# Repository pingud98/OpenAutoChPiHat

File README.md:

# OpenAutoChPiHat
A Raspberry Pi Hat designed for open hardware and open software car sharing

It's now featured in the SEEED fusion gallery: https://www.seeedstudio.com/Open-Car-Sharing-Hardware-Module-OpenAuto-c-g-1036303

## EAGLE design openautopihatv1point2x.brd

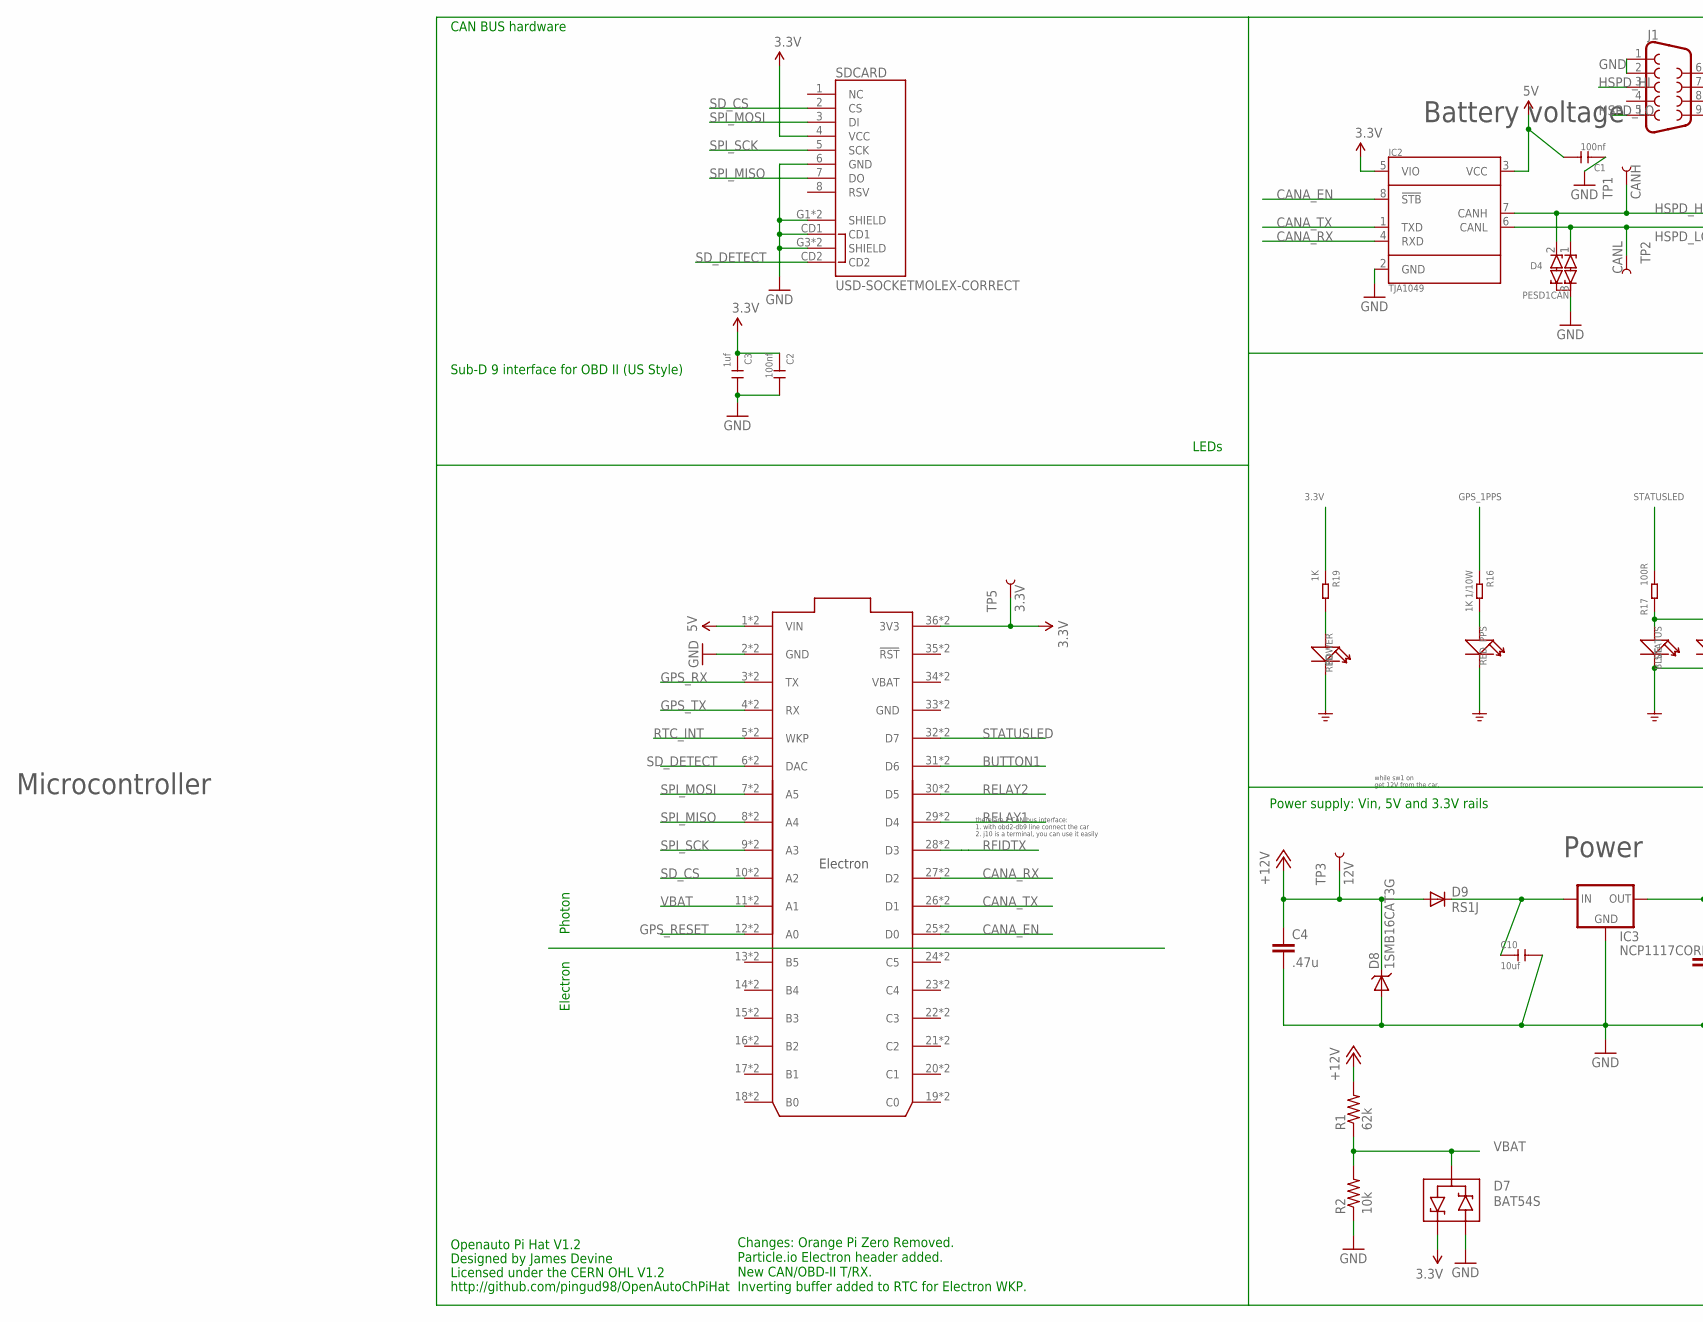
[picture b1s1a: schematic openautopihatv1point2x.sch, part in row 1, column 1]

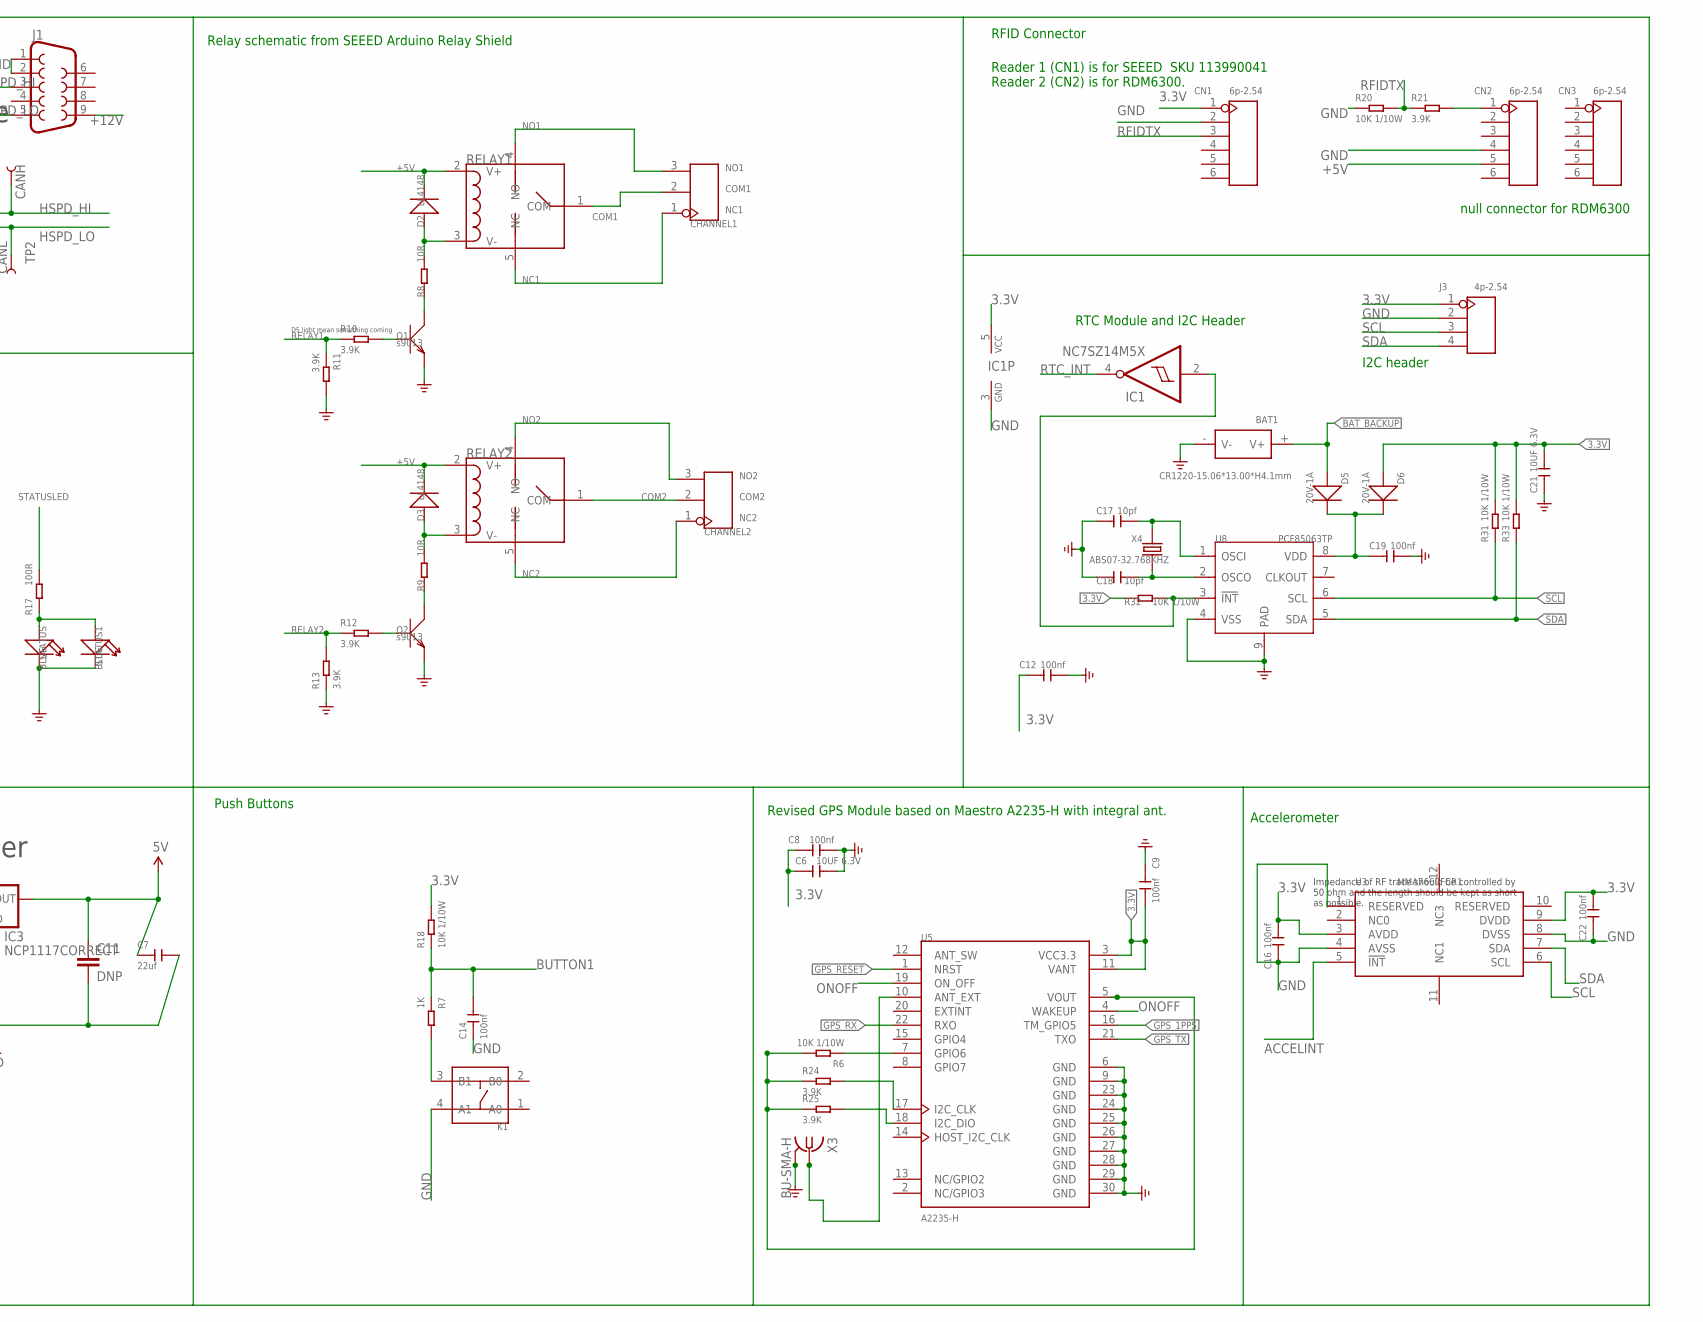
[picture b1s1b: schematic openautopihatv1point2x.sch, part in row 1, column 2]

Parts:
BAT1: CR1220-15.06*13.00*H4.1mm; BAT2P-SMD-16.4-CR1220
C1, C2: 100nf; C0603; PARTNO 08055C104KAT2A
C3: 1uf; C0603; PARTNO CC0805KKX7R7BB105
C4: .47u; C0805; PARTNO C0805C474K5RACTU
C6, C21: 10UF 6.3V; C0603
C7: 22uf; C0805; PARTNO GRM219R61A226MEA0D
C8, C9, C12, C14, C16, C19, C22: 100nf; C0603
C10: 10uf; C0805; PARTNO GRM21BR6YA106KE43L
C11: DNP; C0805; PARTNO GRM219R61A226MEA0D
C17, C18: 10pf; C0603
CHANNEL1, CHANNEL2: SCREW-TERMINAL-3P'3.5'; 3P-3.5
CN1, CN2, CN3: 6p-2.54; H6-2.54
D2, D3: LL4148; LL-34
D4: PESD1CAN; SOT23; PARTNO PESD1CAN-215
D5, D6: 20V-1A; SOD-123
D7: BAT54S; SOT23; PARTNO BAT54S-7-F
D8: 1SMB16CAT3G; SMB-DIODE; PARTNO 1SMB16CAT3G
D9: RS1J; SMA-DIODE; PARTNO RS1J-E3/5AT
ELECTRON: ELECTRON_WITH_EXTERNAL_HEADERS; ELECTRON_EXTERNAL; PARTNO PPTC181LFBN-RC
IC1: NC7SZ14M5X; SOT23-5
IC2: TJA1049; SO8; PARTNO TJA1049T-118
IC3: NCP1117CORRECT; SOT223; PARTNO NCP1117LPST50T3G
J1: DB9MALE; DB9_MALE
J3: 4p-2.54; H4-2.54
K1: DIP-SWITCH-TACTILE-SPST-NO/TS-1109(4P-D6.0MM)'TS-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; SW4-6.0X6.0X5.0MM
POWER: RED; LED-0603
PPS: RED; LED-0603
Q1, Q2: s9013; SOT23
R1: 62k; R0805; PARTNO ERJ-6ENF6202V
R2: 10k; R0805; PARTNO ERJ-6ENF1002V
R6, R18, R20, R31, R32, R33: 10K 1/10W; R0603
R7, R19: 1K; R0603
R8, R9: 10R; R0603
R10, R11, R12, R13, R21, R24, R25: 3.9K; R0603
R16: 1K 1/10W; R0603
R17: 100R; R0603
RELAY1, RELAY2: RELAY-HLS8L-DC5V-S-C; 5P-19.0X15.5X15.8H
SDCARD: USD-SOCKETMOLEX-CORRECT; MICRO-SD-MOLEX-CORRECT; PARTNO 1040310811
STATUS, STATUS1: BLUE; LED-0603
TP1: CANH; PAD.03X.03
TP2: CANL; PAD.03X.03
TP3: 12V; PAD.03X.03
TP5: 3.3V; PAD.03X.03
U3: MMA7660FCR1; DFN10-0.5-3.0X3.0MM
U5: A2235-H; XCVR_A2235-H
U8: PCF85063TP; HWSON8-0.5-2X3X0.75MM
X3: BU-SMA-H
X4: ABS07-32.768KHZ; X2-SMD-3.2X1.5X0.55MM

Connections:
3.3V: C2.1, C3.1, C6.1, C8.1, C9.2, C12.1, C16.2, C21.2, C22.2, CN1.1, D6.+, D7.2 (C1), ELECTRON.36 (3V3), ELECTRON.@36 (3V3), IC1.5 (VCC), IC2.5 (VIO), J3.1, R18.2, R19.1, R31.2, R32.1, R33.2, SDCARD.4 (VCC), TP5.P$1, U3.3 (AVDD), U3.9 (DVDD), U5.3 (VCC3.3), U5.11 (VANT)
5V: C1.2, C7.1, C11.1, ELECTRON.1 (VIN), ELECTRON.@1 (VIN), IC2.3 (VCC), IC3.2 (OUT), IC3.4 (OUT)
!RTC_INT: IC1.2 (I), R32.2, U8.3 (!INT)
+5V: CN2.5, D2.C (-), D3.C (-), RELAY1.2 (V+), RELAY2.2 (V+)
+12V: C4.1, D8.C, D9.A, J1.9, R1.2, TP3.P$1
ACCELINT: U3.5 (!INT)
BAT_BACKUP: BAT1.+ (V+), D5.+
BUTTON1: C14.2, ELECTRON.31 (D6), ELECTRON.@31 (D6), R7.1, R18.1
CANA_EN: ELECTRON.25 (D0), ELECTRON.@25 (D0), IC2.8 (!STB)
CANA_RX: ELECTRON.27 (D2), ELECTRON.@27 (D2), IC2.4 (RXD)
CANA_TX: ELECTRON.26 (D1), ELECTRON.@26 (D1), IC2.1 (TXD)
COM1: CHANNEL1.2, RELAY1.1 (COM)
COM2: CHANNEL2.2, RELAY2.1 (COM)
GND: BAT1.- (V-), C1.1, C2.2, C3.2, C4.2, C6.2, C7.2, C8.2, C9.1, C10.2, C11.2, C12.2, C14.1, C16.1, C17.1, C18.1, C19.2, C21.1, C22.1, CN1.2, CN2.4, D4.3 (COM), D7.1 (A2), D8.A, ELECTRON.2 (GND), ELECTRON.33 (GND), ELECTRON.@2 (GND), ELECTRON.@33 (GND), IC1.3 (GND), IC2.2 (GND), IC3.1 (GND), J1.1, J1.2, J3.2, K1.4 (A1), POWER.-, PPS.-, Q1.2 (E), Q2.2 (E), R2.1, R11.2, R13.1, R20.1, SDCARD.6 (GND), SDCARD.CD1, SDCARD.G1 (SHIELD), SDCARD.G2 (SHIELD), SDCARD.G3 (SHIELD), SDCARD.G4 (SHIELD), STATUS.-, STATUS1.-, U3.1 (RESERVED), U3.4 (AVSS), U3.8 (DVSS), U5.6 (GND), U5.9 (GND), U5.23 (GND), U5.24 (GND), U5.25 (GND), U5.26 (GND), U5.27 (GND), U5.28 (GND), U5.29 (GND), U5.30 (GND), U8.4 (VSS), U8.9 (PAD), X3.2, X3.3 (2), X3.4 (2), X3.5 (2)
GPS_1PPS: R16.1, U5.16 (TM_GPIO5)
GPS_RESET: ELECTRON.12 (A0), ELECTRON.@12 (A0), U5.1 (NRST)
GPS_RX: ELECTRON.3 (TX), ELECTRON.@3 (TX), U5.22 (RXO)
GPS_TX: ELECTRON.4 (RX), ELECTRON.@4 (RX), U5.21 (TXO)
HSPD_HI: D4.2 (C2), IC2.7 (CANH), J1.3, TP1.P$1
HSPD_LO: D4.1 (C1), IC2.6 (CANL), J1.5, TP2.P$1
unnamed: K1.3 (B1), R7.2
unnamed: Q2.1 (B), R12.2
unnamed: D3.A (+), R9.2, RELAY2.3 (V-)
unnamed: Q1.3 (C), R8.1
unnamed: D2.A (+), R8.2, RELAY1.3 (V-)
unnamed: Q2.3 (C), R9.1
unnamed: PPS.+, R16.2
unnamed: R17.2, STATUS.+, STATUS1.+
unnamed: U5.10 (ANT_EXT), X3.1
unnamed: R6.2, R24.1, R25.1, U5.5 (VOUT)
unnamed: R6.1, U5.7 (GPIO6)
unnamed: Q1.1 (B), R10.2
unnamed: CN2.1, R21.2
unnamed: R24.2, U5.17 (I2C_CLK)
unnamed: R25.2, U5.18 (I2C_DIO)
unnamed: POWER.+, R19.2
unnamed: C18.2, U8.2 (OSCO), X4.1
unnamed: C17.2, U8.1 (OSCI), X4.2
unnamed: C10.1, D9.C, IC3.3 (IN)
unnamed: C19.1, D5.-, D6.-, U8.8 (VDD)
NC1: CHANNEL1.1, RELAY1.5 (NC)
NC2: CHANNEL2.1, RELAY2.5 (NC)
NO1: CHANNEL1.3, RELAY1.4 (NO)
NO2: CHANNEL2.3, RELAY2.4 (NO)
ONOFF: U5.4 (WAKEUP), U5.19 (ON_OFF)
RELAY1: ELECTRON.29 (D4), ELECTRON.@29 (D4), R10.1, R11.1
RELAY2: ELECTRON.30 (D5), ELECTRON.@30 (D5), R12.1, R13.2
RFIDTX: CN1.3, ELECTRON.28 (D3), ELECTRON.@28 (D3), R20.2, R21.1
RTC_INT: ELECTRON.5 (WKP), ELECTRON.@5 (WKP), IC1.4 (O)
SCL: J3.3, R31.1, U3.6 (SCL), U8.6 (SCL)
SDA: J3.4, R33.1, U3.7 (SDA), U8.5 (SDA)
SD_CS: ELECTRON.10 (A2), ELECTRON.@10 (A2), SDCARD.2 (CS)
SD_DETECT: ELECTRON.6 (DAC), ELECTRON.@6 (DAC), SDCARD.CD2
SPI_MISO: ELECTRON.8 (A4), ELECTRON.@8 (A4), SDCARD.7 (DO)
SPI_MOSI: ELECTRON.7 (A5), ELECTRON.@7 (A5), SDCARD.3 (DI)
SPI_SCK: ELECTRON.9 (A3), ELECTRON.@9 (A3), SDCARD.5 (SCK)
STATUSLED: ELECTRON.32 (D7), ELECTRON.@32 (D7), R17.1
VBAT: D7.3 (COM), ELECTRON.11 (A1), ELECTRON.34 (VBAT), ELECTRON.@11 (A1), ELECTRON.@34 (VBAT), R1.1, R2.2

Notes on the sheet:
D5 light mean something coming
CAN BUS hardware
there are 2 CAN bus interface:
1. with obd2-db9 line connect the car
2. j10 is a terminal, you can use it easily
Sub-D 9 interface for OBD II (US Style)
get 12V from the car,
while sw1 on
Relay schematic from SEEED Arduino Relay Shield
RFID Connector
Reader 1 (CN1) is for SEEED SKU 113990041 Reader 2 (CN2) is for RDM6300.
RTC Module and I2C Header
Impedance of RF trace should be controlled by 50 ohm and the length should be kept as short as possible.
Revised GPS Module based on Maestro A2235-H with integral ant.
LEDs
Openauto Pi Hat V1.2
Designed by James Devine
Licensed under the CERN OHL V1.2
http://github.com/pingud98/OpenAutoChPiHat
Changes: Orange Pi Zero Removed. Particle.io Electron header added. New CAN/OBD-II T/RX. Inverting buffer added to RTC for Electron WKP.
Push Buttons
Accelerometer
Power supply: Vin, 5V and 3.3V rails
null connector for RDM6300
I2C header
Battery voltage
Microcontroller
Power
Photon
Electron

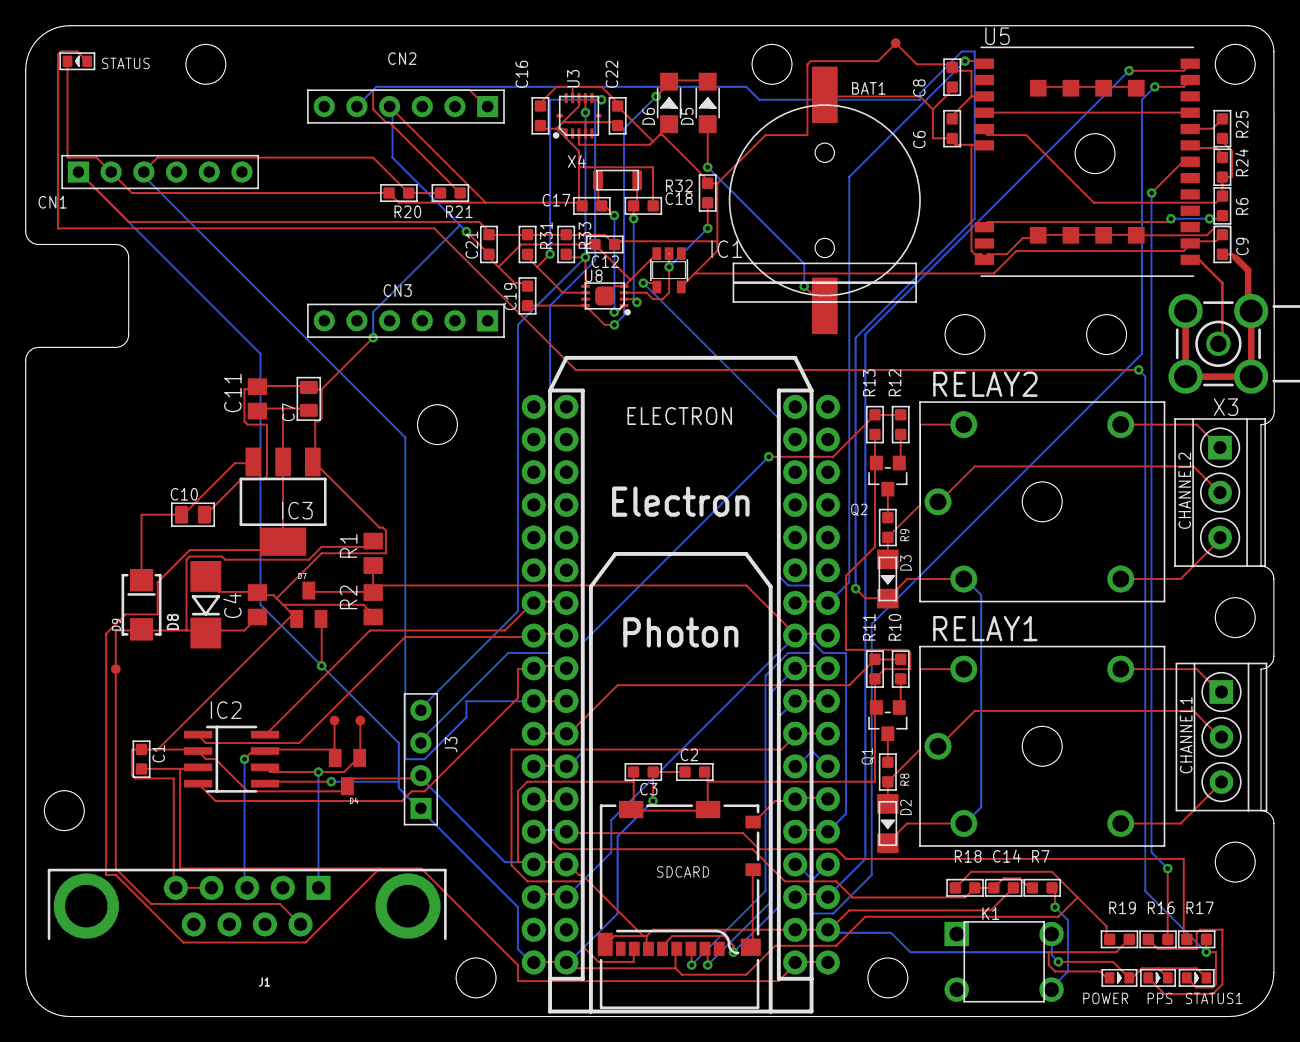
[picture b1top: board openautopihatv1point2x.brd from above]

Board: 2 copper layers, 97.0 x 77.0 mm, 78 parts (0 on the bottom side), 57 nets.

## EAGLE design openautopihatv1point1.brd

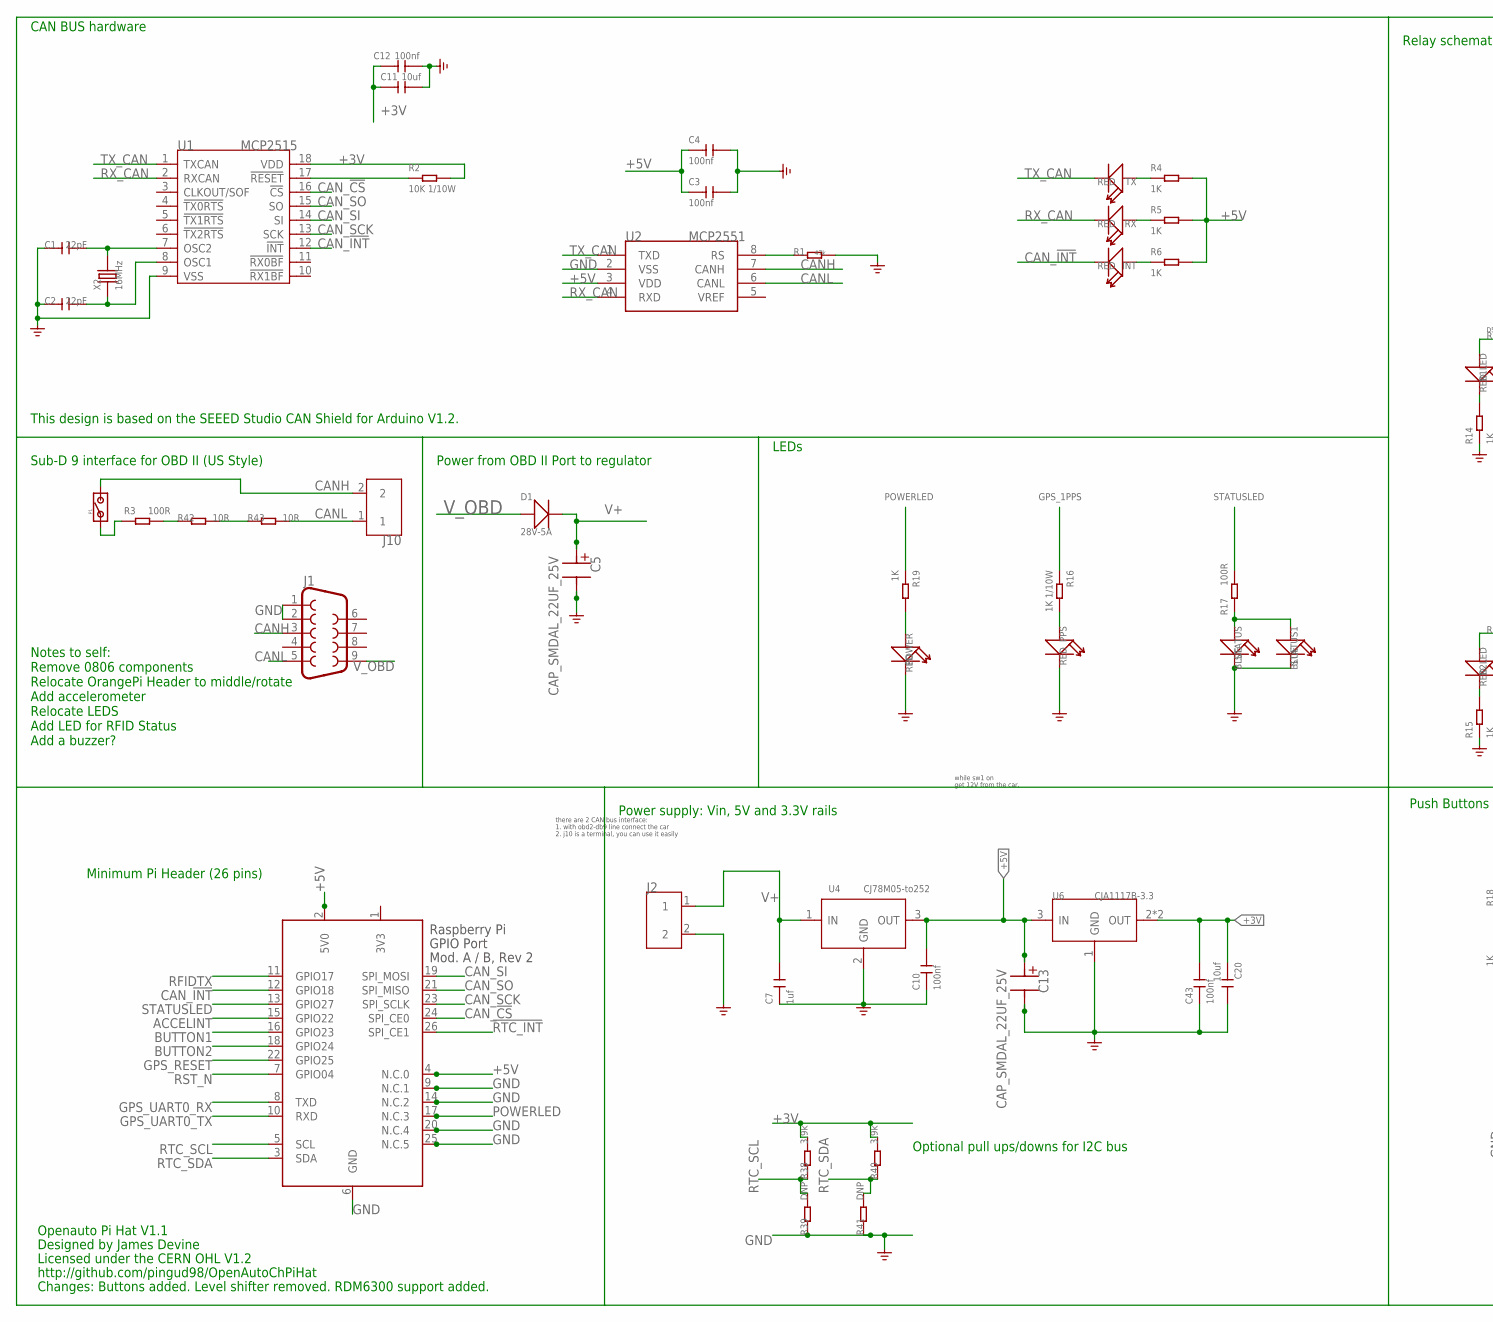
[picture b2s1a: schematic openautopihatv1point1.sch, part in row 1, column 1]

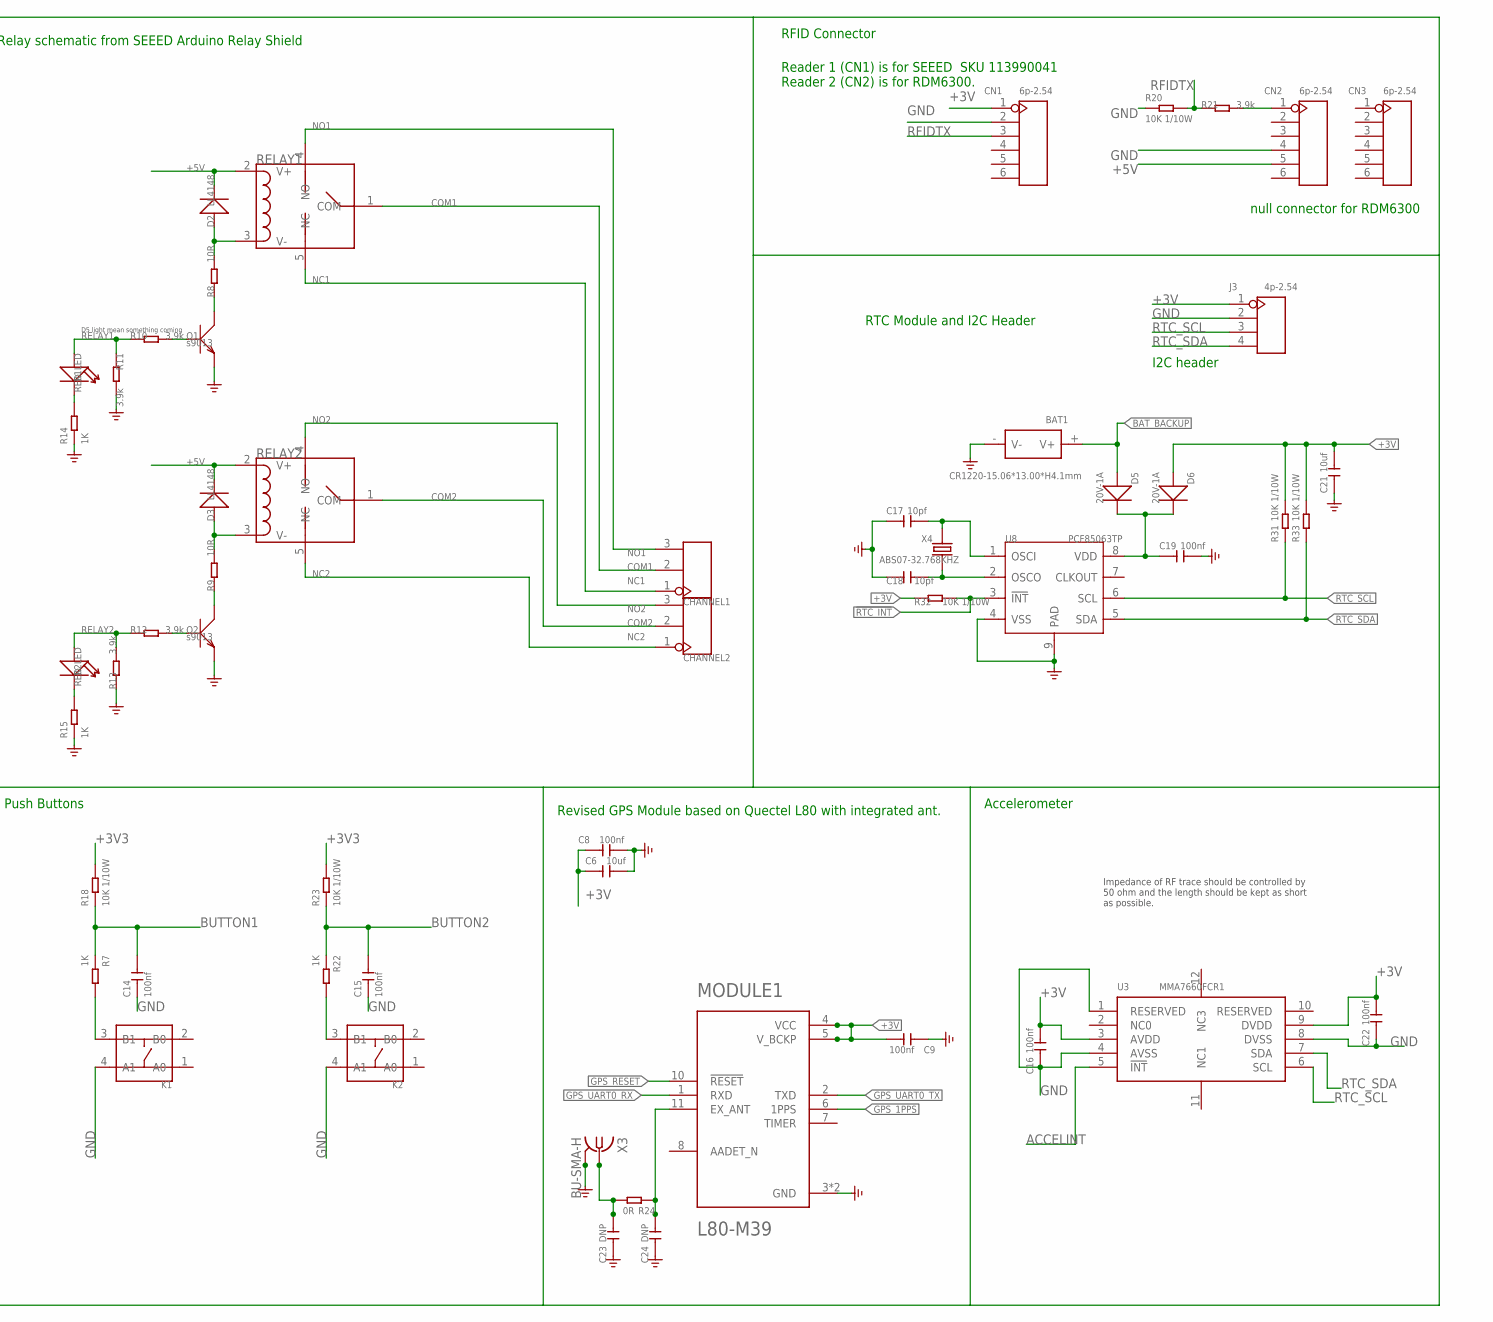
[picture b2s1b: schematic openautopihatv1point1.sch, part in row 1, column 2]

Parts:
BAT1: CR1220-15.06*13.00*H4.1mm; BAT2P-SMD-16.4-CR1220
C1, C2: 22pF; C0603
C3, C4, C8, C9, C10, C12, C14, C15, C16, C19, C22, C43: 100nf; C0603
C5, C13: CAP_SMDAL_22UF_25V; CAP_SMD_AL_D50
C6, C11, C20, C21: 10uf; C0805
C7: 1uf; C0603
C17, C18: 10pf; C0603
C23, C24: DNP; C0603
CHANNEL1, CHANNEL2: SCREW-TERMINAL-3P'3.5'; 3P-3.5
CN1, CN2, CN3: 6p-2.54; H6-2.54
D1: 28V-5A; DO-214AA
D2, D3: LL4148; LL-34
D5, D6: 20V-1A; SOD-123
INT: RED; LED-0603
J1: DB9MALE; DB9_MALE
J2, J10: SCREW-TERMINAL-2P5.0; 2P-5.0
J3: 4p-2.54; H4-2.54
K1, K2: DIP-SWITCH-TACTILE-SPST-NO/TS-1109(4P-D6.0MM)'TS-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; SW4-6.0X6.0X5.0MM
MODULE1: L80-M39; QUECTEL_L80-M39
P1: PAD-JUMPER-2P; 2P-SMD-1.78X1.27
POWER: RED; LED-0603
PPS: RED; LED-0603
Q1, Q2: s9013; SOT23
R1: 47k; 0603
R1LED, R2LED: RED; LED-0603
R2, R18, R20, R23, R31, R32, R33: 10K 1/10W; R0603
R3, R17: 100R; R0603
R4, R5, R6, R7, R14, R15, R19, R22: 1K; R0603
R8, R9, R42, R43: 10R; R0603
R10, R11, R12, R13, R21, R38, R40: 3.9k; R0603
R16: 1K 1/10W; R0603
R24: 0R; R0603
R39, R41: DNP; R0603
RELAY1, RELAY2: RELAY-HLS8L-DC5V-S-C; 5P-19.0X15.5X15.8H
RX: RED; LED-0603
STATUS, STATUS1: BLUE; LED-0603
TX: RED; LED-0603
U1: MCP2515; SOIC18
U2: MCP2551; SOIC8-6.0
U3: MMA7660FCR1; DFN10-0.5-3.0X3.0MM
U4: CJ78M05-to252; TO-252
U6: CJA1117B-3.3; SOT-89
U8: PCF85063TP; HWSON8-0.5-2X3X0.75MM
X1: RASPI_GPIO_AB_PIN
X2: 16MHz; HC49/S
X3: BU-SMA-H
X4: ABS07-32.768KHZ; X2-SMD-3.2X1.5X0.55MM

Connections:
3V3: X1.1 (3V3)
!RTC_INT: R32.2, U8.3 (!INT), X1.26 (SPI_CE1)
+3V: C6.1, C8.1, C9.2, C11.1, C12.1, C16.2, C20.1, C21.2, C22.2, C43.2, CN1.1, D6.+, J3.1, MODULE1.4 (VCC), MODULE1.5 (V_BCKP), R2.2, R31.2, R32.1, R33.2, R38.2, R40.2, U1.18 (VDD), U3.3 (AVDD), U3.9 (DVDD), U6.2 (OUT), U6.4 (OUT)
+3V3: R18.2, R23.2
+5V: C3.1, C4.1, C10.2, C13.P$P, CN2.5, D2.C (-), D3.C (-), R4.2, R5.2, R6.2, RELAY1.2 (V+), RELAY2.2 (V+), U2.3 (VDD), U4.3 (OUT), U6.3 (IN), X1.2 (5V0), X1.4 (N.C.0)
ACCELINT: U3.5 (!INT), X1.15 (GPIO22)
BAT_BACKUP: BAT1.+ (V+), D5.+
BUTTON1: C14.2, R7.1, R18.1, X1.16 (GPIO23)
BUTTON2: C15.2, R22.1, R23.1, X1.18 (GPIO24)
CANH: J1.3, J10.2, P1.2, U2.7 (CANH)
CANL: J1.5, J10.1, R43.2, U2.6 (CANL)
CAN_!CS: U1.16 (!CS), X1.24 (SPI_CE0)
CAN_!INT: INT.-, U1.12 (!INT), X1.12 (GPIO18)
CAN_SCK: U1.13 (SCK), X1.23 (SPI_SCLK)
CAN_SI: U1.14 (SI), X1.19 (SPI_MOSI)
CAN_SO: U1.15 (SO), X1.21 (SPI_MISO)
COM1: CHANNEL1.2, RELAY1.1 (COM)
COM2: CHANNEL2.2, RELAY2.1 (COM)
GND: BAT1.- (V-), C1.1, C2.1, C3.2, C4.2, C5.P$M, C6.2, C7.1, C8.2, C9.1, C10.1, C11.2, C12.2, C13.P$M, C14.1, C15.1, C16.1, C17.1, C18.1, C19.2, C20.2, C21.1, C22.1, C23.1, C24.1, C43.1, CN1.2, CN2.4, J1.1, J1.2, J2.2, J3.2, K1.4 (A1), K2.4 (A1), MODULE1.3 (GND), MODULE1.12 (GND), POWER.-, PPS.-, Q1.2 (E), Q2.2 (E), R1.2, R11.2, R13.1, R14.1, R15.1, R20.1, R39.1, R41.1, STATUS.-, STATUS1.-, U1.9 (VSS), U2.2 (VSS), U3.1 (RESERVED), U3.4 (AVSS), U3.8 (DVSS), U4.2 (GND), U6.1 (GND), U8.4 (VSS), U8.9 (PAD), X1.6 (GND), X1.9 (N.C.1), X1.14 (N.C.2), X1.20 (N.C.4), X1.25 (N.C.5), X3.2, X3.3 (2), X3.4 (2), X3.5 (2)
GPS_1PPS: MODULE1.6 (1PPS), R16.1
GPS_RESET: MODULE1.10 (!RESET), X1.22 (GPIO25)
GPS_UART0_RX: MODULE1.1 (RXD), X1.8 (TXD)
GPS_UART0_TX: MODULE1.2 (TXD), X1.10 (RXD)
unnamed: K1.3 (B1), R7.2
unnamed: R4.1, TX.+
unnamed: Q2.1 (B), R12.2
unnamed: D3.A (+), R9.2, RELAY2.3 (V-)
unnamed: Q1.3 (C), R8.1
unnamed: D2.A (+), R8.2, RELAY1.3 (V-)
unnamed: Q2.3 (C), R9.1
unnamed: PPS.+, R16.2
unnamed: R17.2, STATUS.+, STATUS1.+
unnamed: R3.1, R42.1
unnamed: R1LED.-, R14.2
unnamed: R2LED.-, R15.2
unnamed: C24.2, MODULE1.11 (EX_ANT), R24.1
unnamed: R5.1, RX.+
unnamed: C1.2, U1.7 (OSC2), X2.2
unnamed: C2.2, U1.8 (OSC1), X2.1
unnamed: C23.2, R24.2, X3.1
unnamed: INT.+, R6.1
unnamed: R1.1, U2.8 (RS)
unnamed: Q1.1 (B), R10.2
unnamed: CN2.1, R21.2
unnamed: K2.3 (B1), R22.2
unnamed: POWER.+, R19.2
unnamed: P1.1, R3.2
unnamed: C18.2, U8.2 (OSCO), X4.1
unnamed: C17.2, U8.1 (OSCI), X4.2
unnamed: R42.2, R43.1
unnamed: C19.1, D5.-, D6.-, U8.8 (VDD)
NC1: CHANNEL1.1, RELAY1.5 (NC)
NC2: CHANNEL2.1, RELAY2.5 (NC)
NO1: CHANNEL1.3, RELAY1.4 (NO)
NO2: CHANNEL2.3, RELAY2.4 (NO)
POWERLED: R19.1, X1.17 (N.C.3)
RELAY1: R1LED.+, R10.1, R11.1
RELAY2: R2LED.+, R12.1, R13.2
RFIDTX: CN1.3, R20.2, R21.1, X1.11 (GPIO17)
RST_N: R2.1, U1.17 (!RESET), X1.7 (GPIO04)
RTC_SCL: J3.3, R31.1, R38.1, R39.2, U3.6 (SCL), U8.6 (SCL), X1.5 (SCL)
RTC_SDA: J3.4, R33.1, R40.1, R41.2, U3.7 (SDA), U8.5 (SDA), X1.3 (SDA)
RX_CAN: RX.-, U1.2 (RXCAN), U2.4 (RXD)
STATUSLED: R17.1, X1.13 (GPIO27)
TX_CAN: TX.-, U1.1 (TXCAN), U2.1 (TXD)
V+: C5.P$P, C7.2, D1.-, J2.1, U4.1 (IN)
V_OBD: D1.+, J1.9

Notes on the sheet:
D5 light mean something coming
CAN BUS hardware
there are 2 CAN bus interface:
1. with obd2-db9 line connect the car
2. j10 is a terminal, you can use it easily
Sub-D 9 interface for OBD II (US Style)
get 12V from the car,
while sw1 on
Power from OBD II Port to regulator
This design is based on the SEEED Studio CAN Shield for Arduino V1.2.
Relay schematic from SEEED Arduino Relay Shield
RFID Connector
Reader 1 (CN1) is for SEEED SKU 113990041 Reader 2 (CN2) is for RDM6300.
RTC Module and I2C Header
Impedance of RF trace should be controlled by 50 ohm and the length should be kept as short as possible.
Revised GPS Module based on Quectel L80 with integrated ant.
Minimum Pi Header (26 pins)
LEDs
Optional pull ups/downs for I2C bus
Openauto Pi Hat V1.1
Designed by James Devine
Licensed under the CERN OHL V1.2
http://github.com/pingud98/OpenAutoChPiHat
Changes: Buttons added. Level shifter removed. RDM6300 support added.
Push Buttons
Accelerometer
Power supply: Vin, 5V and 3.3V rails
null connector for RDM6300
Notes to self: Remove 0806 components Relocate OrangePi Header to middle/rotate Add accelerometer Relocate LEDS Add LED for RFID Status Add a buzzer?
I2C header

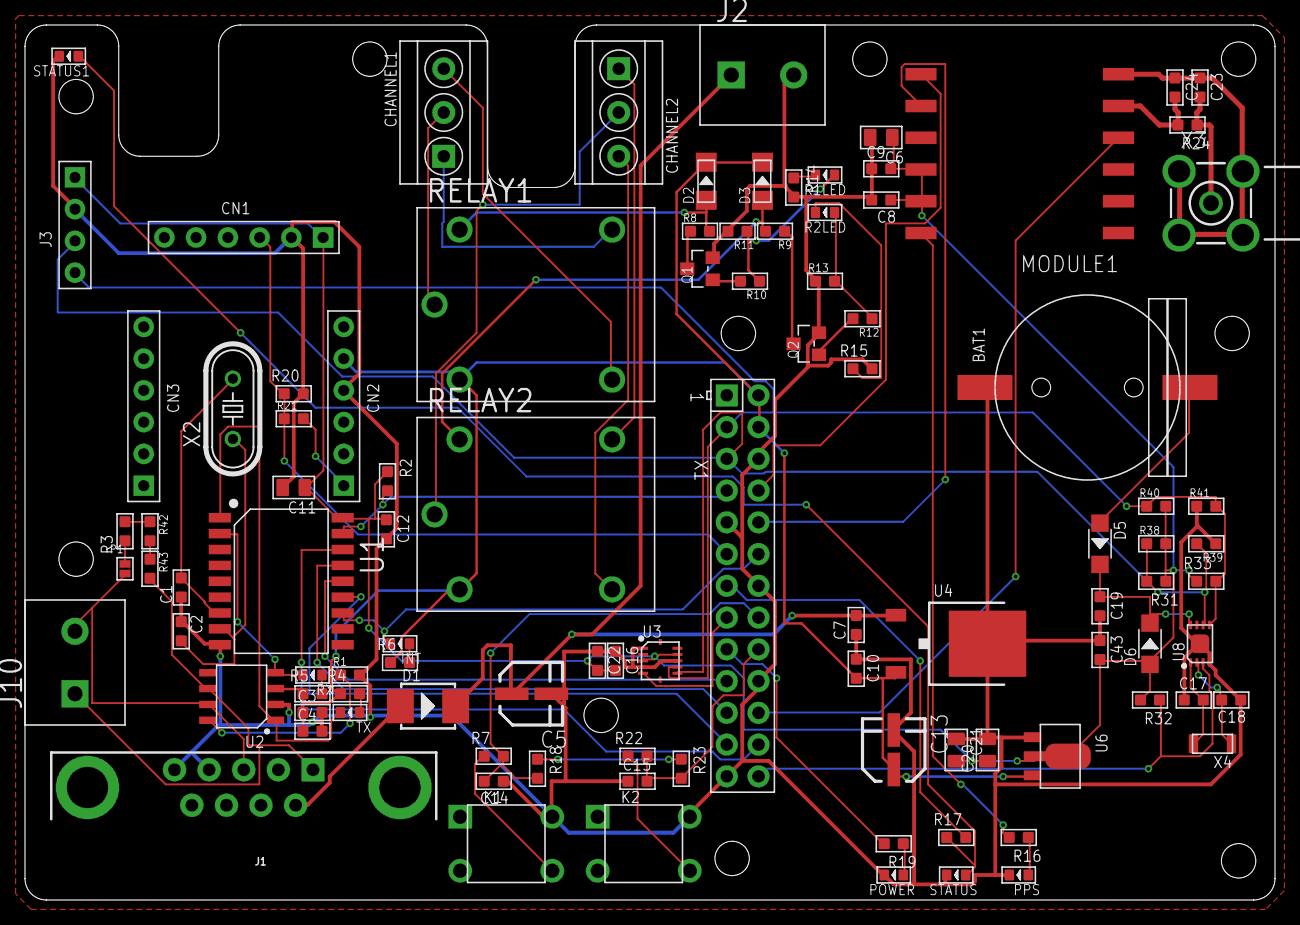
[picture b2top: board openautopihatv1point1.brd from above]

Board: 2 copper layers, 100.0 x 70.0 mm, 100 parts (0 on the bottom side), 66 nets.

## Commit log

2017-08-02 EagleCad Schematic for main board
    First draft, incomplete.
2017-08-16 Schematic revised & completed. Layout in progress
2017-08-16 added library, errors during compilation.
2017-10-29 As prototypes manufactured
2017-11-13 Added BOM
    For production at SEEED studio
2017-11-20 Updated schematic based on hardware debug. Layout to follow.
2017-11-23 Version 1.1 design completed
2017-12-10 Respin with Photon/Electron hardware

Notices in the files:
parts and their libraries:
SparkFun-Connectors: Licensing: Creative Commons ShareAlike 4.0 International - https://creativecommons.org/licenses/by-sa/4.0
SparkFun-Aesthetics: Licensing: CC v3.0 Share-Alike You are welcome to use this library for commercial purposes.
